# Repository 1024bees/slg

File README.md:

# Sweet little guy

I wanted to make a friend to talk to, this is my sweet little guy.

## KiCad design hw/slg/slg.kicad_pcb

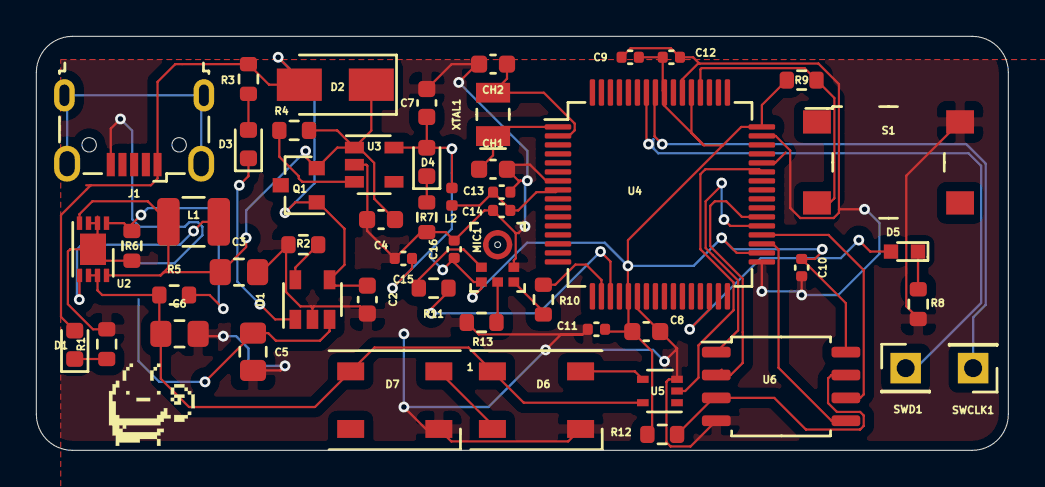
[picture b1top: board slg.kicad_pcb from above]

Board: 4 copper layers, 54.0 x 23.0 mm, 53 parts (1 on the bottom side), 35 nets.

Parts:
C2, C4, C7: 1u; C_0603_1608Metric
C3, C5: 4.7u; C_0805_2012Metric_Pad1.18x1.45mm_HandSolder
C6: 10uF; C_0805_2012Metric_Pad1.18x1.45mm_HandSolder
C8: 4u7; C_0603_1608Metric
C9, C10, C11, C12, C14, C15, C16: 100n; C_0402_1005Metric
C13: 1u; C_0402_1005Metric
CH1, CH2: 15pf; C_0603_1608Metric
D1, D3: RED; LED_0603_1608Metric
D2: B120-E3; D_SMA
D4: GREEN; LED_0603_1608Metric
D5: LTST-C190GKT; LED_0603
D6, D7: WS2812B; LED_WS2812B_PLCC4_5.0x5.0mm_P3.2mm
J1: USB_B_Micro; USB_Micro-B_Wuerth_629105150521
J2: Conn_01x02_Male; JST_PH_B2B-PH-SM4-TB_1x02-1MP_P2.00mm_Vertical
L1: 4.7uH; L_1210_3225Metric
L2: 27n; L_0402_1005Metric
MIC1: SPH0645LM4H-B
Q1: AO3401A; SOT-23
R1, R3, R4, R7: 1k5; R_0603_1608Metric
R2: 2k; R_0603_1608Metric
R5: 976k; R_0603_1608Metric
R6: 309k; R_0603_1608Metric
R8, R9: 10k; R_0603_1608Metric
R10, R11: 25; R_0603_1608Metric
R12, R13: 100k; R_0603_1608Metric
S1: PTS645SM43SMTR92_LFS; Switch_Tactile_SMD_6x6mm_PTS645
SWCLK1: Conn_01x01_Male; PinHeader_1x01_P2.54mm_Vertical
SWD1: Conn_01x01_Male; PinHeader_1x01_P2.54mm_Vertical
U1: MCP73831-2-OT; SOT-23-5
U2: MCP1640BMC; DFN-8-1EP_3x2mm_P0.5mm_EP1.75x1.45mm
U3: AP2112K-3.3; SOT-23-5
U4: ATSAMD51J20A-A; TQFP-64_10x10mm_P0.5mm
U5: SN74LV1T34DCK; SOT-353_SC-70-5
U6: SST25VF080B-50-4x-S2Ax; SOIC-8_5.275x5.275mm_P1.27mm
XTAL1: ECS-_327-12_5-34B-TR; SMD-2_3.2x1.5mm

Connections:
+3.3VA: C13.1, C14.1, L2.2, U4.8
+3V3: C7.1, C8.1, C9.1, C10.1, C11.1, C12.1, C15.1, C16.1, D4.2, L2.1, MIC1.5, R9.1, R12.1, U3.5, U4.21, U4.34, U4.48, U4.53, U4.56, U6.8
+5V: C6.1, D6.1, D7.1, R5.1, U2.6, U2.7, U5.5
/MCU /FLASH_DI: U4.38, U6.2
/MCU /FLASH_DO: U4.35, U6.5
/MCU /FLASH_SCK: U4.36, U6.6
/MCU /I2S_WS: R10.2, U4.18
/Periphals/FLASH_CE: U4.37, U6.1
/Periphals/I2S_BCLK: R11.1, U4.19
/Periphals/LEDIN: U4.43, U5.2
GND: C2.2, C3.2, C4.2, C5.2, C6.2, C7.2, C8.2, C9.2, C10.2, C11.2, C12.2, C13.2, C14.2, C15.2, C16.2, CH1.2, CH2.2, D6.3, D7.3, J1.5, J2.1, MIC1.2, MIC1.3, R1.2, R2.2, R6.2, R7.2, R8.2, R13.1, S1.2, U1.2, U2.2, U2.3, U2.9, U3.2, U4.7, U4.22, U4.33, U4.47, U4.54, U5.3, U6.4
unnamed: D1.1, R1.1
unnamed: D3.1, U1.1
unnamed: D3.2, R3.1
unnamed: D4.1, R7.1
unnamed: D5.1, R8.1
unnamed: D5.2, U4.30
unnamed: D6.2, D7.4
unnamed: D6.4, U5.4
unnamed: L1.2, U2.5
unnamed: MIC1.1, R10.1
unnamed: MIC1.4, R11.2
unnamed: MIC1.6, R13.2
unnamed: R2.1, U1.5
unnamed: R4.1, U3.3
unnamed: R5.2, R6.1, U2.1
unnamed: R12.2, U6.3, U6.7
RESET: R9.2, S1.3, U4.52
SWCLK: SWCLK1.1, U4.57
SWD: SWD1.1, U4.58
VBATT: C5.1, J2.2, U1.3
VIN: C3.1, C4.1, D2.1, L1.1, Q1.2, R4.2, U2.4, U2.8, U3.1
VUSB: C2.1, D1.2, D2.2, J1.1, Q1.1, R3.2, U1.4
XIN32: CH1.1, U4.1, XTAL1.1
XOUT32: CH2.1, U4.2, XTAL1.2

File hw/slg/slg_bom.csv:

"Id";"Designator";"Package";"Quantity";"Designation";"Supplier and ref";
1;"G***";"beefin";1;"LOGO";;;
2;"U6";"SOIC-8_5.275x5.275mm_P1.27mm";1;"SST25VF080B-50-4x-S2Ax";;;
3;"U4";"TQFP-64_10x10mm_P0.5mm";1;"ATSAMD51J20A-A";;;
4;"SWD1,SWCLK1";"PinHeader_1x01_P2.54mm_Vertical";2;"Conn_01x01_Male";;;
5;"J2";"JST_PH_B2B-PH-SM4-TB_1x02-1MP_P2.00mm_Vertical";1;"Conn_01x02_Male";;;
6;"D7,D6";"LED_WS2812B_PLCC4_5.0x5.0mm_P3.2mm";2;"WS2812B";;;
7;"C7,C4,C2";"C_0603_1608Metric";3;"1u";;;
8;"XTAL1";"SMD-2_3.2x1.5mm";1;"ECS-_327-12_5-34B-TR";;;
9;"U5";"SOT-353_SC-70-5";1;"SN74LV1T34DCK";;;
10;"U3";"SOT-23-5";1;"AP2112K-3.3";;;
11;"U2";"DFN-8-1EP_3x2mm_P0.5mm_EP1.75x1.45mm";1;"MCP1640BMC";;;
12;"U1";"SOT-23-5";1;"MCP73831-2-OT";;;
13;"S1";"Switch_Tactile_SMD_6x6mm_PTS645";1;"PTS645SM43SMTR92_LFS";;;
14;"R13,R12";"R_0603_1608Metric";2;"100k";;;
15;"R11,R10";"R_0603_1608Metric";2;"25";;;
16;"R9,R8";"R_0603_1608Metric";2;"10k";;;
17;"R7,R4,R3,R1";"R_0603_1608Metric";4;"1k5";;;
18;"R6";"R_0603_1608Metric";1;"309k";;;
19;"R5";"R_0603_1608Metric";1;"976k";;;
20;"R2";"R_0603_1608Metric";1;"2k";;;
21;"Q1";"SOT-23";1;"AO3401A";;;
22;"MIC1";"SPH0645LM4H-B";1;"SPH0645LM4H-B";;;
23;"L2";"L_0402_1005Metric";1;"27n";;;
24;"L1";"L_1210_3225Metric";1;"4.7uH";;;
25;"J1";"USB_Micro-B_Wuerth_629105150521";1;"USB_B_Micro";;;
26;"D5";"LED_0603";1;"LTST-C190GKT";;;
27;"D4";"LED_0603_1608Metric";1;"GREEN";;;
28;"D3,D1";"LED_0603_1608Metric";2;"RED";;;
29;"D2";"D_SMA";1;"B120-E3";;;
30;"CH2,CH1";"C_0603_1608Metric";2;"15pf";;;
31;"C16,C15,C14,C12,C11,C10,C9";"C_0402_1005Metric";7;"100n";;;
32;"C13";"C_0402_1005Metric";1;"1u";;;
33;"C8";"C_0603_1608Metric";1;"4u7";;;
34;"C6";"C_0805_2012Metric_Pad1.18x1.45mm_HandSolder";1;"10uF";;;
35;"C5,C3";"C_0805_2012Metric_Pad1.18x1.45mm_HandSolder";2;"4.7u";;;
